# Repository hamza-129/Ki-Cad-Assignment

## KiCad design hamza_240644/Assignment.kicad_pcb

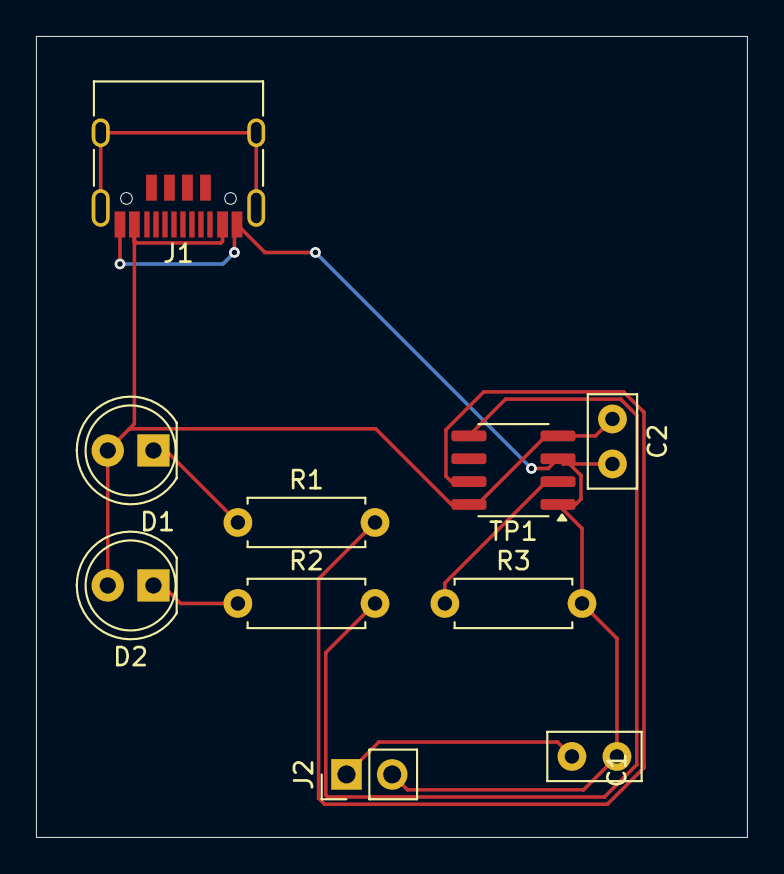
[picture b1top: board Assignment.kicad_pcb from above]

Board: 2 copper layers, 39.5 x 44.5 mm, 10 parts (0 on the bottom side), 8 nets.

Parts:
C1, C2: 10 uf; C_Disc_D5.0mm_W2.5mm_P2.50mm
D1, D2: LED; LED_D5.0mm
J1: USB_C_Receptacle_PowerOnly_6P; USB_C_Receptacle_HRO_TYPE-C-31-M-12
J2: Conn_01x02_Pin; PinHeader_1x02_P2.54mm_Vertical
R1, R2: 100; R_Axial_DIN0207_L6.3mm_D2.5mm_P7.62mm_Horizontal
R3: 10k; R_Axial_DIN0207_L6.3mm_D2.5mm_P7.62mm_Horizontal
TP1: SOIC-8_3.9x4.9mm_P1.27mm

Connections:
GND: C1.2, C2.2, J1.A12 (GND), J1.B12 (GND), J2.2, R3.2, TP1.1 (TEMP), TP1.3 (GND)
unnamed: D1.1 (K), R1.1
unnamed: D2.1 (K), R2.1
unnamed: R1.2, TP1.7 (CHRG)
unnamed: R3.1, TP1.2 (PROG)
unnamed: R2.2, TP1.5 (STDBY)
VCC: C2.1, D1.2 (A), D2.2 (A), J1.A9 (VBUS), J1.B9 (VBUS), TP1.4 (Vcc), TP1.8 (CE)
VD: C1.1, J2.1

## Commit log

2025-05-24 Initial commit of KiCAD Assignment
2025-05-28 Final submission
